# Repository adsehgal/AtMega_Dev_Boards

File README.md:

# Custom AtMega Development Boards
### Aditya Sehgal

</p>This repo is a compilation of custom development boards I have taken upon myself to design. These boards house the AtMega family of microcontrollers and are similar to Arduino boards, however, with personal customizations as follows:</p>
 <il>   

- Reduce the physical size of the reference Arduinos by roughly half.
- Implement USB-C for future proofing.
- Remove unnecessary components.
 <il>
<br>

</p>The gerber files can be sent to JLCPCB.com for manufacturing since they agree with their constraints and the components can be ordered via LCSC.com using the BOMs provided.<br>
Hand soldering the PCBs may come across as a bit of a challenge for some since it requires parctice with QFP packages as well as 3225 packaged crystal oscillators with pads on the bottom. Both of these are easily solderable if you have access to a hot air station, but definitely doable with a temperature controlled iron and a well tip.<br>
The BOMs can be simply uploaded to LCSC using their BOM tool to add all required components directly to cart. Note to be made here, header pins are not included in the BOM since I want to leave the choice of male/female up to the designer.</p>

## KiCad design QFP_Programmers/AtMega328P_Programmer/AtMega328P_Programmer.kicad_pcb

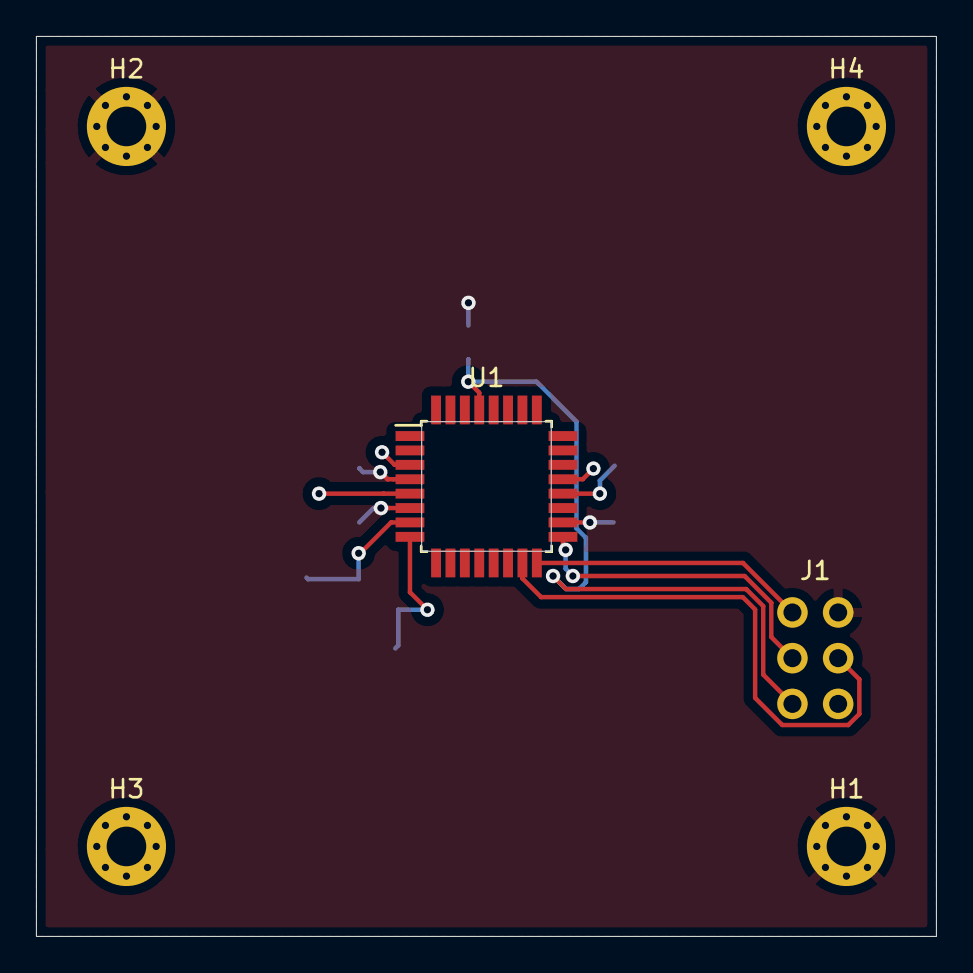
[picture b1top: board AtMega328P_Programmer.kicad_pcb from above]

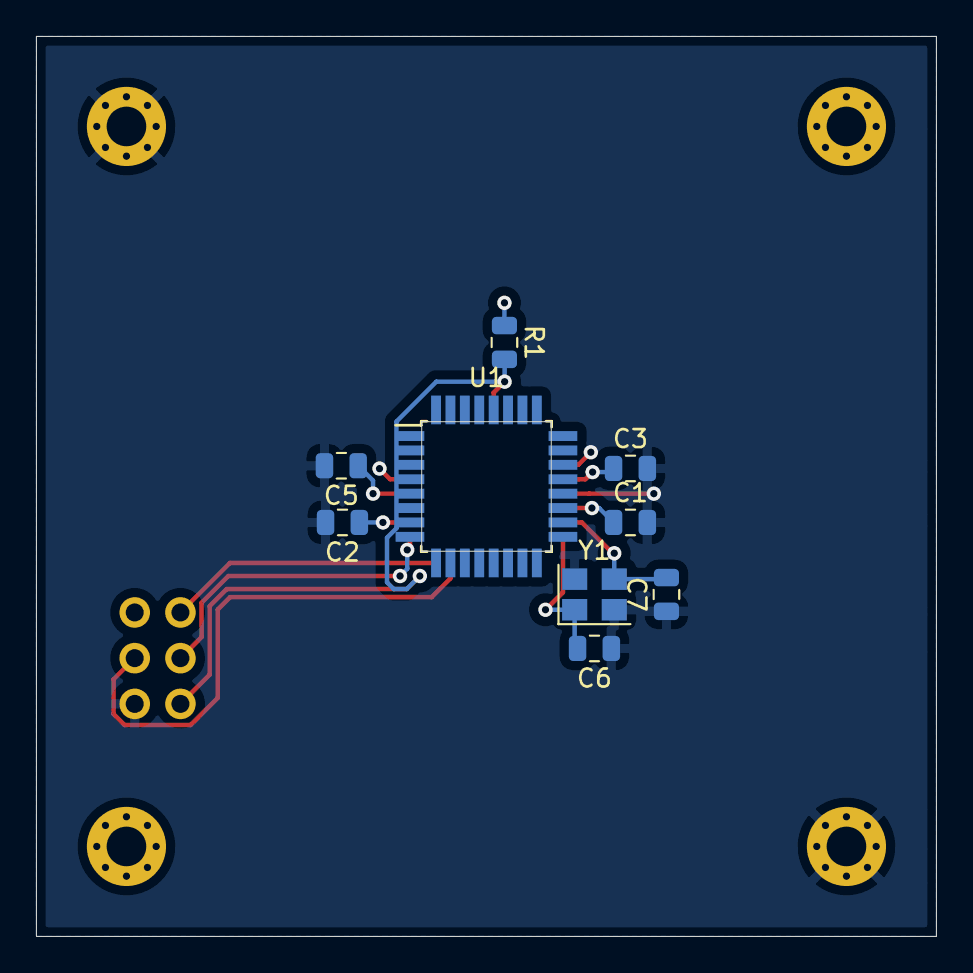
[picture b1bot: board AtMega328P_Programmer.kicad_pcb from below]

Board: 2 copper layers, 50.0 x 50.0 mm, 15 parts (9 on the bottom side), 9 nets.

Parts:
C1, C2, C3, C5: 100nF; C_0805_2012Metric
C6, C7: 22pF; C_0805_2012Metric
H1, H2, H3, H4: MountingHole_Pad; MountingHole_2.2mm_M2_Pad_Via
J1: ICSP; PinHeader_2x03_P2.54mm_Vertical
R1: 10K; R_0805_2012Metric
U1, U1#2: ATmega328P-AU; TQFP-32_7x7mm_P0.8mm
Y1: 16MHz; Crystal_SMD_3225-4Pin_3.2x2.5mm

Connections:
+5V: C1.1, C2.1, C3.1, H1.1, H2.1, J1.2, R1.1, U1#2.4 (VCC), U1#2.6 (VCC), U1#2.18 (AVCC)
/MISO: J1.1, U1#2.16 (PB4)
/MOSI: J1.4, U1#2.15 (PB3)
/RST: J1.5, R1.2, U1#2.29 (~RESET~/PC6)
/SCK: J1.3, U1#2.17 (PB5)
GNDREF: C1.2, C2.2, C3.2, C5.2, C6.1, C7.1, H3.1, H4.1, J1.6, U1#2.3 (GND), U1#2.5 (GND), U1#2.21 (GND), Y1.2, Y1.4
unnamed: C5.1, U1#2.20 (AREF)
unnamed: C6.2, U1#2.8 (XTAL2/PB7), Y1.1
unnamed: C7.2, U1#2.7 (XTAL1/PB6), Y1.3

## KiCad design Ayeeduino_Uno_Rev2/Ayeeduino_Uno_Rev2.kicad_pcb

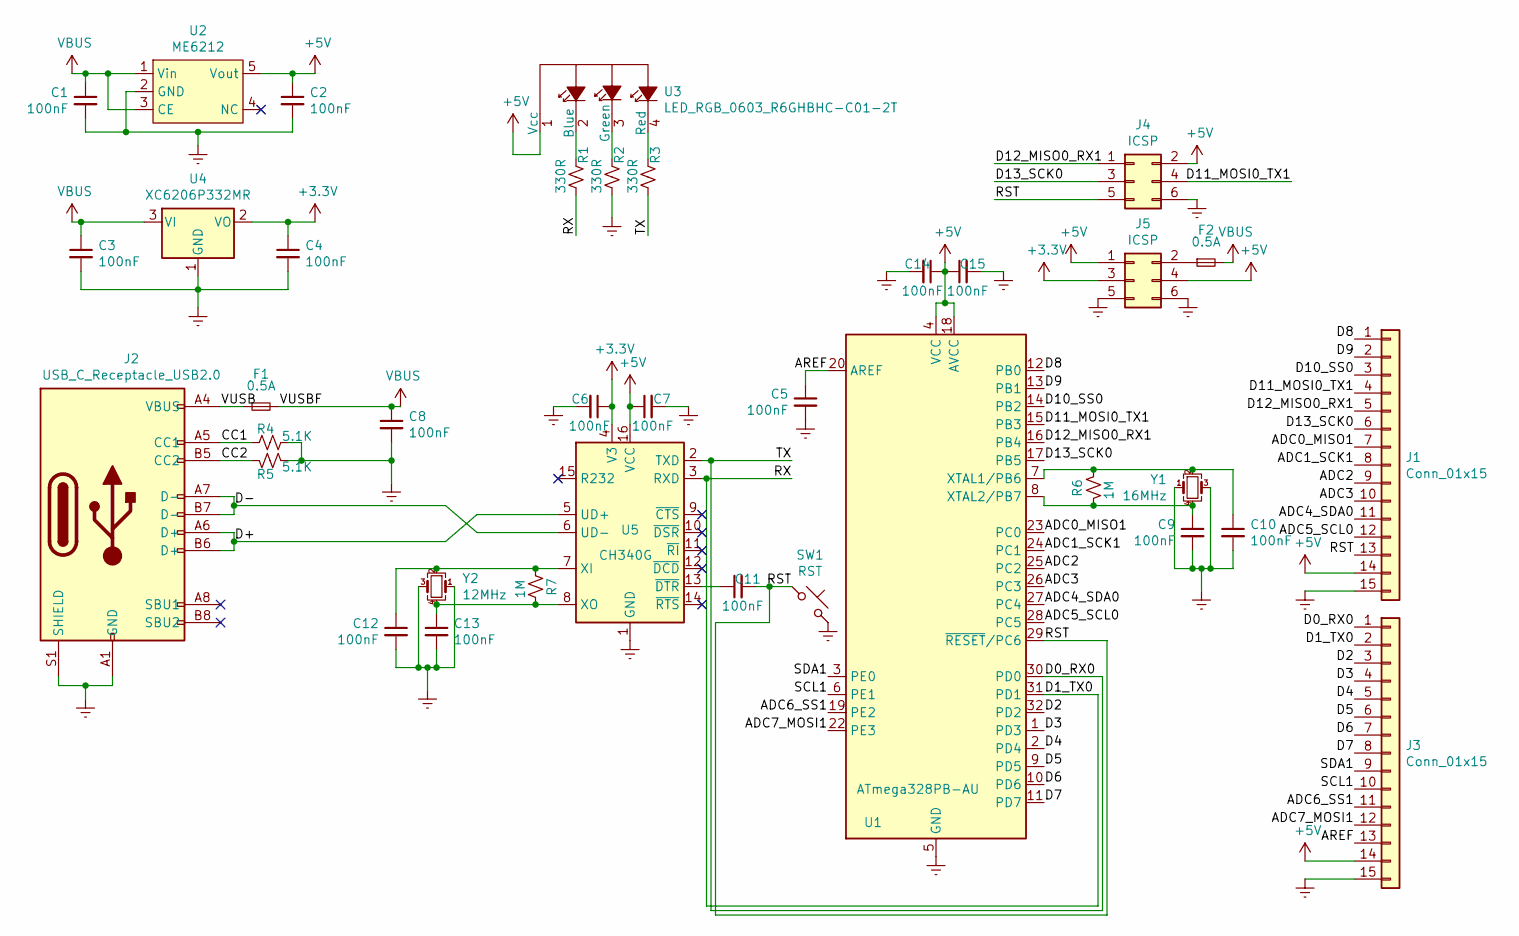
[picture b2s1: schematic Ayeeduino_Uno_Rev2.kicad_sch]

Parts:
C1, C2, C3, C4, C5, C6, C7, C8, C9, C10, C11, C12, C13, C14, C15: 100nF; C_0603_1608Metric
F1, F2: 0.5A; Fuse_0603_1608Metric_Castellated
J1, J3: Conn_01x15; PinHeader_1x15_P2.54mm_Vertical
J2: USB_C_Receptacle_USB2.0; USB_C_Receptacle_XKB_U262-16XN-4BVC11
J4, J5: ICSP; PinHeader_2x03_P2.54mm_Vertical
R1, R2, R3: 330R; R_0603_1608Metric
R4, R5: 5.1K; R_0603_1608Metric
R6, R7: 1M; R_0603_1608Metric
SW1: RST; SW_SPST_TL3342
U1: ATmega328PB-AU; TQFP-32_7x7mm_P0.8mm
U2: ME6212; SOT-23-5
U3: LED_RGB_0603_R6GHBHC-C01-2T; LED_DUAL_0603
U4: XC6206P332MR; SOT-23
U5: CH340G; SOIC-16_3.9x9.9mm_P1.27mm
Y1: 16MHz; Crystal_SMD_3225-4Pin_3.2x2.5mm
Y2: 12MHz; Crystal_SMD_3225-4Pin_3.2x2.5mm

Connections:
+3V3: C4.1, C6.1, J5.3, U4.2 (VO), U5.4 (V3)
+5V: C2.1, C7.1, C14.1, C15.1, J1.14, J3.14, J4.2, J5.1, J5.4, U1.4 (VCC), U1.18 (AVCC), U2.5 (Vout), U3.1 (Vcc), U5.16 (VCC)
/ADC0_MISO1: J1.7, U1.23 (PC0)
/ADC1_SCK1: J1.8, U1.24 (PC1)
/ADC2: J1.9, U1.25 (PC2)
/ADC3: J1.10, U1.26 (PC3)
/ADC4_SDA0: J1.11, U1.27 (PC4)
/ADC5_SCL0: J1.12, U1.28 (PC5)
/ADC6_SS1: J3.11, U1.19 (PE2)
/ADC7_MOSI1: J3.12, U1.22 (PE3)
/AREF: C5.1, J3.13, U1.20 (AREF)
/CC1: J2.A5 (CC1), R4.1
/CC2: J2.B5 (CC2), R5.1
/D0_RX0: J3.1, R3.2, U1.30 (PD0), U5.2 (TXD)
/D1_TX0: J3.2, R1.2, U1.31 (PD1), U5.3 (RXD)
/D2: J3.3, U1.32 (PD2)
/D3: J3.4, U1.1 (PD3)
/D4: J3.5, U1.2 (PD4)
/D5: J3.6, U1.9 (PD5)
/D6: J3.7, U1.10 (PD6)
/D7: J3.8, U1.11 (PD7)
/D8: J1.1, U1.12 (PB0)
/D9: J1.2, U1.13 (PB1)
/D10_SS0: J1.3, U1.14 (PB2)
/D11_MOSI0_TX1: J1.4, J4.4, U1.15 (PB3)
/D12_MISO0_RX1: J1.5, J4.1, U1.16 (PB4)
/D13_SCK0: J1.6, J4.3, U1.17 (PB5)
/D+: J2.A6 (D+), J2.B6 (D+), U5.5 (UD+)
/D-: J2.A7 (D-), J2.B7 (D-), U5.6 (UD-)
/RST: C11.2, J1.13, J4.5, SW1.1, U1.29 (~RESET~/PC6)
/SCL1: J3.10, U1.6 (PE1)
/SDA1: J3.9, U1.3 (PE0)
/VUSB: F1.1, J2.A4 (VBUS), J2.A9 (VBUS), J2.B4 (VBUS), J2.B9 (VBUS)
GNDREF: C1.2, C2.2, C3.2, C4.2, C5.2, C6.2, C7.2, C8.2, C9.2, C10.2, C12.2, C13.2, C14.2, C15.2, J1.15, J2.A1 (GND), J2.A12 (GND), J2.B1 (GND), J2.B12 (GND), J2.S1 (SHIELD), J3.15, J4.6, J5.5, J5.6, R2.2, R4.2, R5.2, SW1.2, U1.5 (GND), U1.21 (GND), U4.1 (GND), U5.1 (GND), Y1.1, Y1.3, Y2.1, Y2.3
unnamed: C9.1, R6.2, U1.8 (XTAL2/PB7), Y1.4
unnamed: C10.1, R6.1, U1.7 (XTAL1/PB6), Y1.2
unnamed: C11.1, U5.13 (~DTR)
unnamed: C12.1, R7.1, U5.7 (XI), Y2.2
unnamed: C13.1, R7.2, U5.8 (XO), Y2.4
unnamed: F2.1, J5.2
unnamed: R1.1, U3.2 (Blue)
unnamed: R2.1, U3.3 (Green)
unnamed: R3.1, U3.4 (Red)
VBUS: C1.1, C3.1, C8.1, F1.2, F2.2, U2.1 (Vin), U2.3 (CE), U4.3 (VI)

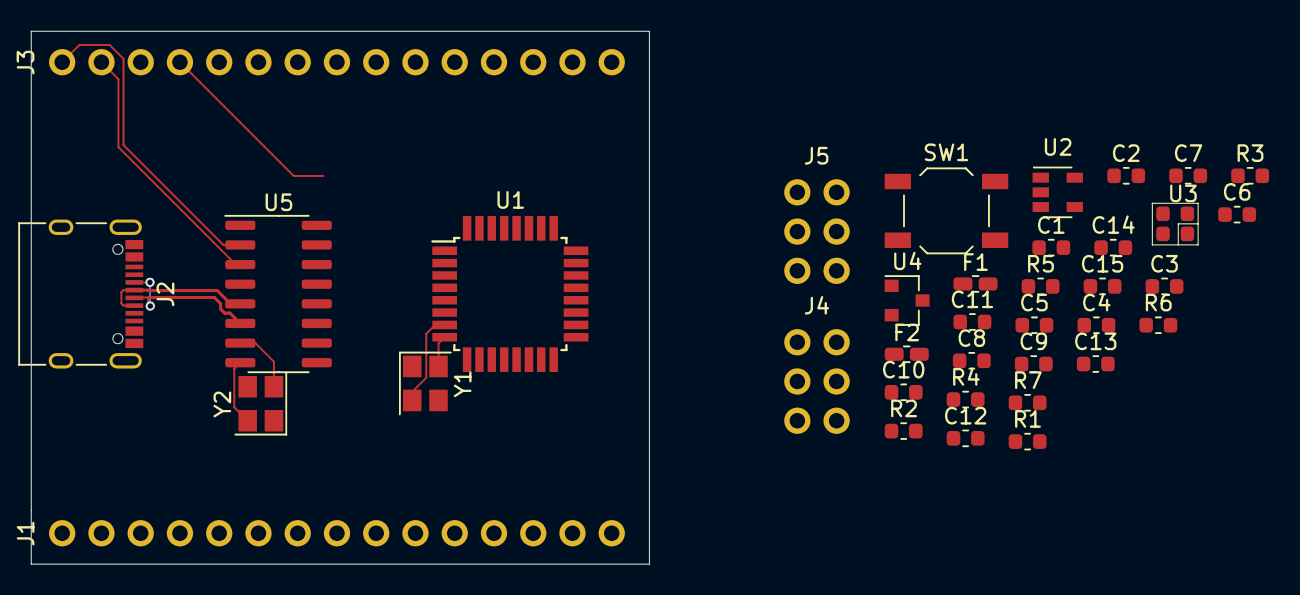
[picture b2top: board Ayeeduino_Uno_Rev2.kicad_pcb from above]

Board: 2 copper layers, 40.0 x 34.5 mm, 37 parts (0 on the bottom side), 44 nets.

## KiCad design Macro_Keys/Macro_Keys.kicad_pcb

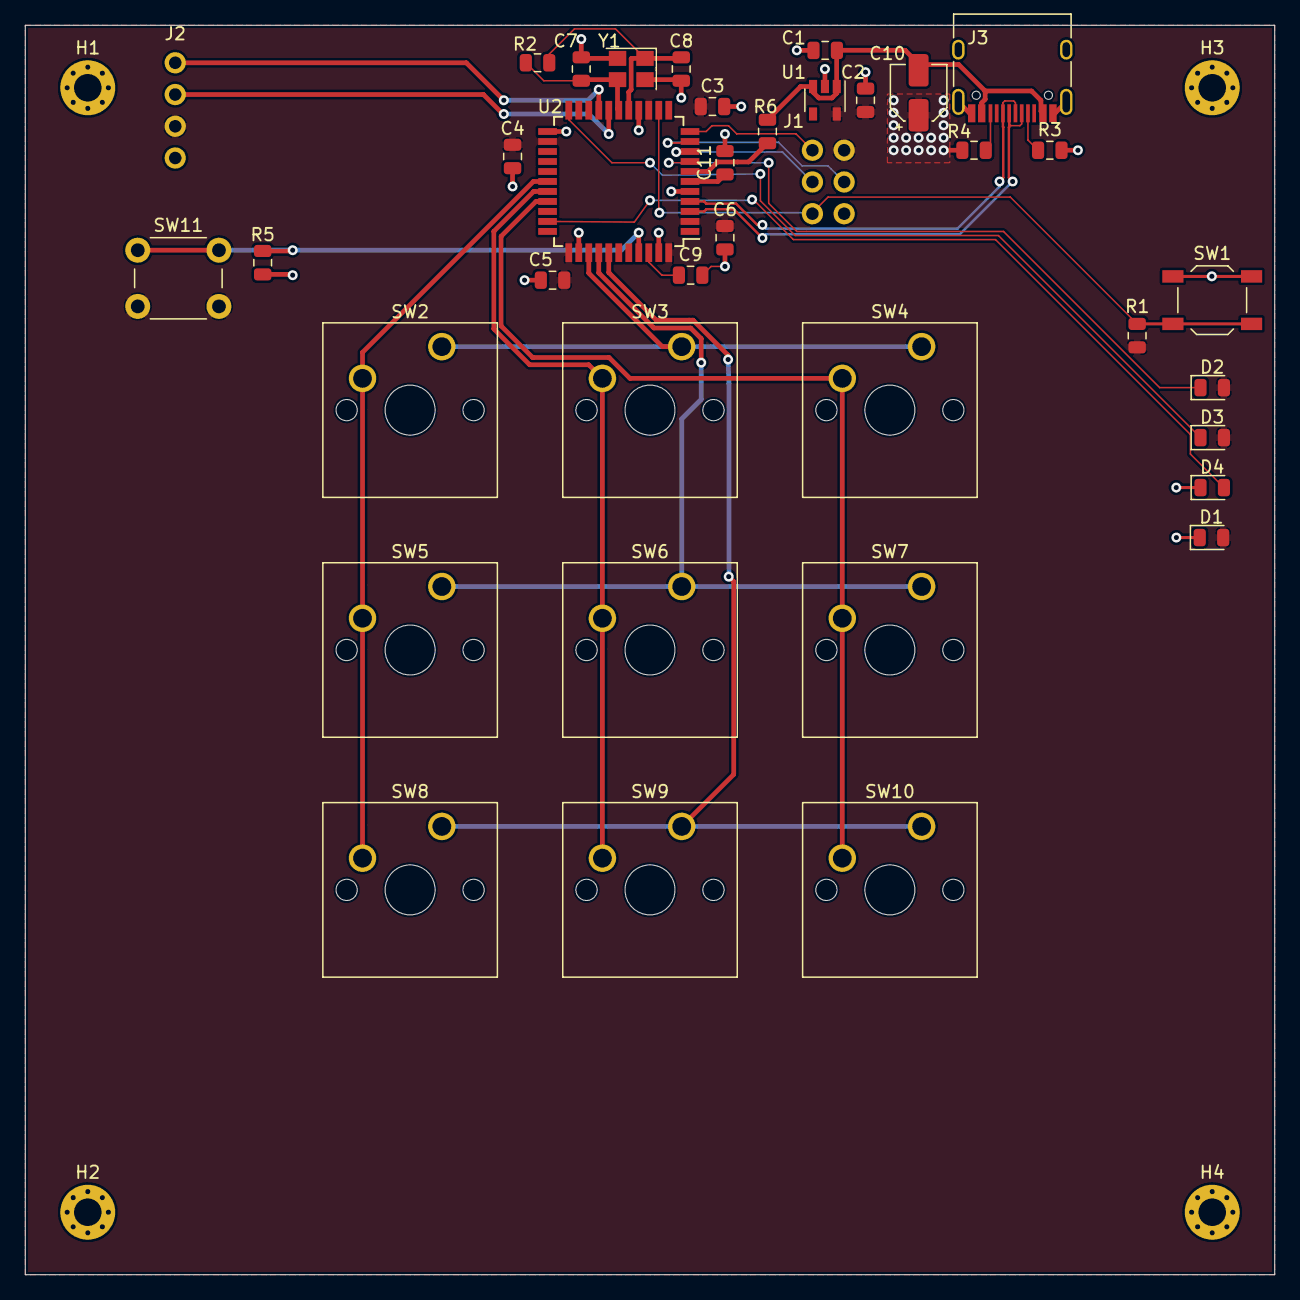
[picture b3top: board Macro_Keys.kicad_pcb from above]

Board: 2 copper layers, 100.0 x 100.0 mm, 42 parts (0 on the bottom side), 28 nets.

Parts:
C1, C2, C3, C4, C5, C6, C9: 100nF; C_0805_2012Metric
C7, C8: 22pF; C_0805_2012Metric
C10: 10uF; CP_Elec_4x5.4
C11: 1uF; C_0805_2012Metric
D1: PWR; LED_0805_2012Metric
D2: RX; LED_0805_2012Metric
D3: TX; LED_0805_2012Metric
D4: D13; LED_0805_2012Metric
H1, H2, H3, H4: MountingHole; MountingHole_2.2mm_M2_Pad_Via
J1: ICSP; PinHeader_2x03_P2.54mm_Vertical
J2: OLED; PinHeader_1x04_P2.54mm_Vertical
J3: USB_C_Receptacle_USB2.0; USB_C_Receptacle_HRO_TYPE-C-31-M-12
R1, R5: 10K; R_0805_2012Metric
R2: 1M; R_0805_2012Metric
R3, R4: 5.1K; R_0805_2012Metric
R6: 0R; R_0805_2012Metric
SW1: RST; SW_SPST_TL3342
SW2, SW3, SW4, SW5, SW6, SW7, SW8, SW9, SW10: SW; SW_Cherry_MX_1.00u_PCB
SW11: Mode; SW_PUSH_6mm
U1: ME6212; SOT-23-5
U2: ATmega32U4-AU; TQFP-44_10x10mm_P0.8mm
Y1: 16MHz; Crystal_SMD_3225-4Pin_3.2x2.5mm

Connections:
+5V: C2.1, C3.1, C4.1, C5.1, C6.1, D1.2 (A), D2.2 (A), D3.2 (A), J1.2, J2.3, R1.2, SW11.2, U1.5 (Vout), U2.2 (UVCC), U2.14 (VCC), U2.24 (AVCC), U2.34 (VCC), U2.44 (AVCC)
/A0: SW2.1, SW3.1, SW4.1, U2.36 (PF7)
/A1: SW5.1, SW6.1, SW7.1, U2.37 (PF6)
/A2: SW8.1, SW9.1, SW10.1, U2.38 (PF5)
/A5: R5.2, SW11.1, U2.41 (PF0)
/C0: SW2.2, SW5.2, SW8.2, U2.28 (PB4)
/C1: SW3.2, SW6.2, SW9.2, U2.29 (PB5)
/C2: SW4.2, SW7.2, SW10.2, U2.30 (PB6)
/CC1: J3.A5 (CC1), R3.1
/CC2: J3.B5 (CC2), R4.1
/D2: J2.1, U2.19 (PD1)
/D3: J2.2, U2.18 (PD0)
/D+: J3.A6 (D+), J3.B6 (D+), U2.4 (D+)
/D-: J3.A7 (D-), J3.B7 (D-), U2.3 (D-)
/IO13: D4.2 (A), U2.32 (PC7)
/MISO: J1.1, U2.11 (PB3)
/MOSI: J1.4, U2.10 (PB2)
/RST: J1.5, R1.1, SW1.2, U2.13 (~RESET)
/RXLED: D2.1 (K), U2.8 (PB0)
/SCK: J1.3, U2.9 (PB1)
/TXLED: D3.1 (K), U2.22 (PD5)
GNDREF: C1.2, C2.2, C3.2, C4.2, C5.2, C6.2, C7.2, C8.2, C9.2, C10.1, C11.2, D1.1 (K), D4.1 (K), J1.6, J2.4, J3.A1 (GND), J3.A12 (GND), J3.B1 (GND), J3.B12 (GND), J3.S1 (SHIELD), R3.2, R4.2, R5.1, SW1.1, U1.2 (GND), U2.5 (UGND), U2.15 (GND), U2.23 (GND), U2.35 (GND), U2.43 (GND), Y1.2, Y1.4
unnamed: C7.1, R2.2, U2.17 (XTAL1), Y1.3
unnamed: C8.1, R2.1, U2.16 (XTAL2), Y1.1
unnamed: C9.1, U2.42 (AREF)
unnamed: C11.1, U2.6 (UCAP)
unnamed: R6.2, U2.7 (VBUS)
VBUS: C1.1, C10.2, J3.A4 (VBUS), J3.A9 (VBUS), J3.B4 (VBUS), J3.B9 (VBUS), R6.1, U1.1 (Vin), U1.3 (CE)

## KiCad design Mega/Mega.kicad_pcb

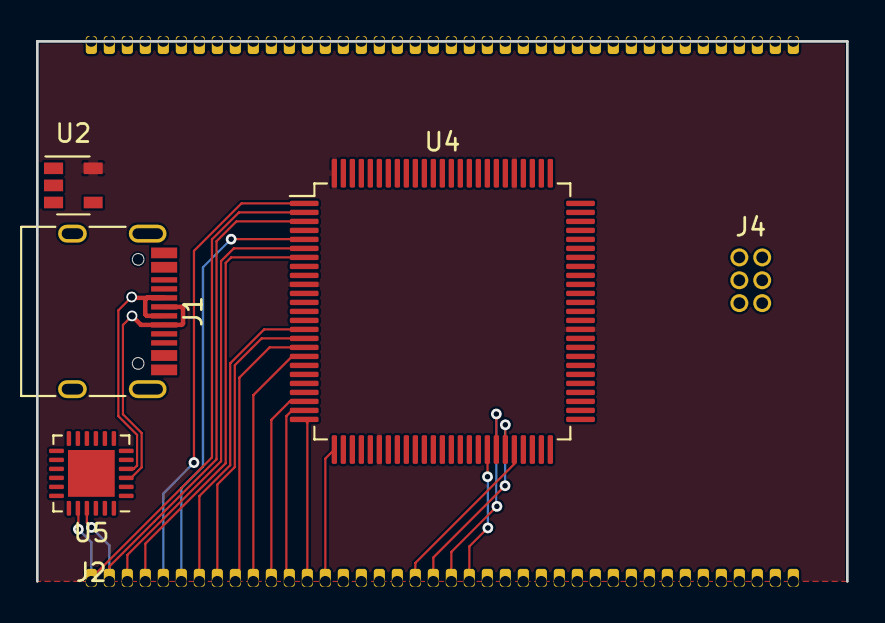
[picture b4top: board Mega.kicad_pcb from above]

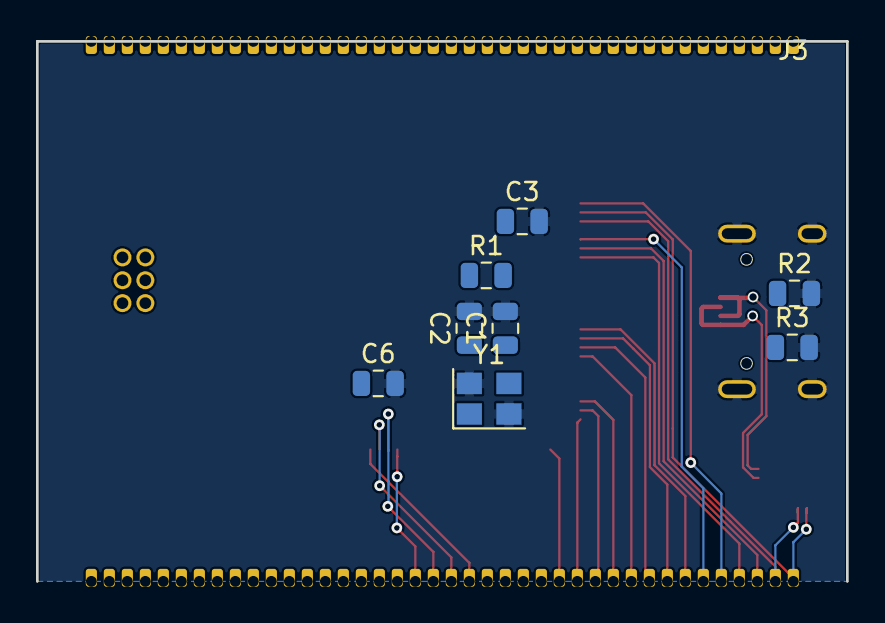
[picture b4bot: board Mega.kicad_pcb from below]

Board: 2 copper layers, 45.0 x 30.0 mm, 15 parts (9 on the bottom side), 81 nets.

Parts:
C1, C2: 22pF; C_0805_2012Metric
C3, C6: 100nF; C_0805_2012Metric
J1: USB_C_Receptacle_USB2.0; USB_C_Receptacle_HRO_TYPE-C-31-M-12
J2, J3: Conn_02x20_Counter_Clockwise; 1x40_1.0mm_Castellations
J4: Conn_02x03_Counter_Clockwise; PinHeader_2x03_P1.27mm_Vertical
R1: 1M; R_0805_2012Metric
R2, R3: 5.1K; R_0805_2012Metric
U2: MIC5205-5.0YM5; SOT-23-5
U4: AtMega2560; LQFP-100_14x14mm_P0.5mm
U5: CP2104; QFN-24-1EP_4x4mm_P0.5mm_EP2.6x2.6mm
Y1: 16MHz; Crystal_SMD_3225-4Pin_3.2x2.5mm

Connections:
+5V: U2.5 (OUT), U4.10 (VCC), U4.31 (VCC), U4.61 (VCC), U4.80 (VCC), U4.100 (AVCC)
/D0: J2.1, U4.2 (PE0), U5.20 (RXD)
/D1: J2.2, U4.3 (PE1), U5.21 (TXD)
/D2: J2.3, U4.6 (PE4)
/D3: J2.4, U4.7 (PE5)
/D4: J2.5, U4.1 (PG5)
/D5: J2.6, U4.5 (PE3)
/D6: J2.7, U4.15 (PH3)
/D7: J2.8, U4.16 (PH4)
/D8: J2.9, U4.17 (PH5)
/D9: J2.10, U4.18 (PH6)
/D10: J2.11, U4.23 (PB4)
/D11: J2.12, U4.24 (PB5)
/D12: J2.13, U4.25 (PB6)
/D13: J2.14, U4.26 (PB7)
/D14: J2.15, U4.64 (PJ1)
/D15: J2.16, U4.63 (PJ0)
/D16: J2.17, U4.13 (PH1)
/D17: J2.18, U4.12 (PH0)
/D18: J2.19, U4.46 (PD3)
/D19: J2.20, U4.45 (PD2)
/D20: J2.21, U4.44 (PD1)
/D21: J2.22, U4.43 (PD0)
/D22: J2.23, U4.78 (PA0)
/D23: J2.24, U4.77 (PA1)
/D24: J2.25, U4.76 (PA2)
/D25: J2.26, U4.75 (PA3)
/D26: J2.27, U4.74 (PA4)
/D27: J2.28, U4.73 (PA5)
/D28: J2.29, U4.72 (PA6)
/D29: J2.30, U4.71 (PA7)
/D30: J2.31, U4.60 (PC7)
/D31: J2.32, U4.59 (PC6)
/D32: J2.33, U4.58 (PC5)
/D33: J2.34, U4.57 (PC4)
/D34: J2.35, U4.56 (PC3)
/D35: J2.36, U4.55 (PC2)
/D36: J2.37, U4.54 (PC1)
/D37: J2.38, U4.53 (PC0)
/D38: J2.39, U4.50 (PD7)
/D39: J2.40, U4.70 (PG2)
/D40: J3.1, U4.52 (PG1)
/D41: J3.2, U4.51 (PG0)
/D42: J3.3, U4.42 (PL7)
/D43: J3.4, U4.41 (PL6)
/D44: J3.5, U4.40 (PL5)
/D45: J3.6, U4.39 (PL4)
/D46: J3.7, U4.38 (PL3)
/D47: J3.8, U4.37 (PL2)
/D48: J3.9, U4.36 (PL1)
/D49: J3.10, U4.35 (PL0)
/D50: J3.11, U4.22 (PB3)
/D51: J3.12, U4.21 (PB2)
/D52: J3.13, U4.20 (PB1)
/D53: J3.14, U4.19 (PB0)
/D70: J3.25, U4.79 (PJ7)
/D71: J3.26, U4.69 (PJ6)
/D72: J3.27, U4.68 (PJ5)
/D73: J3.28, U4.67 (PJ4)
/D74: J3.29, U4.66 (PJ3)
/D75: J3.30, U4.65 (PJ2)
/D76: J3.31, U4.49 (PD6)
/D77: J3.32, U4.48 (PD5)
/D78: J3.33, U4.47 (PD4)
/D79: J3.34, U4.29 (PG4)
/D80: J3.35, U4.28 (PG3)
/D81: J3.36, U4.27 (PH7)
/D82: J3.37, U4.14 (PH2)
/D83: J3.38, U4.9 (PE7)
/D84: J3.39, U4.8 (PE6)
/D85: J3.40, U4.4 (PE2)
/D+: J1.A6 (D+), J1.B6 (D+), U5.3 (D+)
/D-: J1.A7 (D-), J1.B7 (D-), U5.4 (D-)
/RST: U4.30 (~RESET), U5.23 (DTR)
GNDREF: C1.2, C2.2, C3.2, C6.2, J1.A1 (GND), J1.A12 (GND), J1.B1 (GND), J1.B12 (GND), J1.S1 (SHIELD), R2.2, R3.2, U4.11 (GND), U4.32 (GND), U4.62 (GND), U4.81 (GND), U4.99 (GND), Y1.2, Y1.4
unnamed: C1.1, R1.1, U4.34 (XTAL1), Y1.3
unnamed: C2.1, R1.2, U4.33 (XTAL2), Y1.1
unnamed: C3.1, U4.98 (AREF)
unnamed: J1.A5 (CC1), R2.1
unnamed: J1.B5 (CC2), R3.1
VBUS: J1.A4 (VBUS), J1.A9 (VBUS), J1.B4 (VBUS), J1.B9 (VBUS), U2.1 (IN)

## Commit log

2020-03-20 update - empty
2020-03-20 Removed kicad files
2020-03-20 updated gitignore
2020-03-20 ignore updated
2020-03-20 Repositioned reset button - added fourth mounting hole
2020-03-20 Schematic update
2020-03-20 readme update
2020-03-20 Update Uno
2020-03-20 Uno Updates
2020-03-20 Uno Gerber updated
2020-03-20 BOM added
2020-03-20 remove redudancies
2020-03-20 Upload pro mini start
2020-04-10 Repor readme updated
2020-06-26 Started New Aueeduino Uno with 328pb
2020-07-19 working on layout
2020-07-27 Macro_Keys Layout complete + Programmer WIP
2020-08-07 Merge-no major changes
2020-08-28 removed redundancies
